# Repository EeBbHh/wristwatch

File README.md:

Disclaimer. This is a work in progress. Open source proof of concept provided. Screenshots and video provided. Documentation is subject to change.

NOTICE! Due to memory limits a second python file was created. sprites.py is required. Place next to code.py in the CIRCUITPY drive. The follwing lines need to be added to boot.py: "import displayio" and below that "displayio.release_displays()"

Clock + Metronome + Tuner wristwatch is the goal of this project. In addition. There are standalone files for each mode.

Dev Enviornment: Mu https://codewith.mu/en/, KiCAD https://www.kicad.org/

Circuitpython for QTpy RP2040: https://circuitpython.org/board/adafruit_qtpy_rp2040/

Circuitpython 10.x libraries: https://circuitpython.org/libraries

NOTE: Place the following in the lib folder: adafruit_bus_device folder, adafruit_display_text folder, adafruit_gc9a01a.mpy and adafruit_ticks.mpy. 

NOTE: Add the following to the requirements folder: adafruit_bus_device folder, adafruit_display_text folder and adafruit_gc9a01a folder.

Microcontroller: QTpy RP2040 https://www.adafruit.com/product/4900

Special thanks to these two projects that got me started on this journey. https://projecthub.arduino.cc/petbump10/arduino-tick-tock-metronome-a49188 and https://github.com/FoamyGuy/Adafruit_CircuitPython_Display_AnalogClock

Prototype 1, 2 and 3 Display: 1.28" Round TFT https://www.adafruit.com/product/6178 

Prototype 1 hardware: EYESPI BFF https://www.adafruit.com/product/5772, IoT Button BFF https://www.adafruit.com/product/5666, Vibration Mini Motor https://www.adafruit.com/product/1201, Piezo Buzzer https://www.adafruit.com/product/1740, LIPO Charger BFF https://www.adafruit.com/product/5397, 400mAh LIPO Battery https://www.adafruit.com/product/3898

Prototype 2 hardware: IoT Button BFF removed. Prototype board added. SMD parts replace THT parts. All SMD parts purchsed from https://www.digikey.com/ Buttons added. Piezo replaced with magnetic transducer. Schematic and board file provided. 

Prototype 3 hardware: EYESPI BFF removed. Prototype board updated. SMD FPC added. SMD vibration motor replaces THT vibration motor. 420mAh LIPO battery https://www.adafruit.com/product/4236 replaces 400mAh LIPO battery. 

Prototype 4 hardware: Prototype board updated. New 1.28 Display https://www.buydisplay.com/1-28-inch-tft-lcd-display-240x240-round-circle-screen-for-smart-watch, SMD FPC updated. QTpy dock added. Futher refinement is underway as I put protoboardV4 through testing.

Prototype 5 hardware: Circuit for display reset added. Circuit for backlight added. QTpy dock adjusted from 17.5mm to 18mm. Prototype board version 5 sits at 25mm. 

Prototype 6 hardware: Lipo BFF circuitry absorbed to further reduce height of the stack. Final iteration for 6 will have the female headers removed and vibration motor moved out of the way for soldering the QTpy closer to the board. Prototype board version 6 sits at 11.30mm. Goal is to get closer to 13 with case.

Prototype 7 hardware: Through hole side actuated buttons replaced Surface mount top actuated buttons. Test pads replaced through hole connectors for battery.

https://github.com/user-attachments/assets/00a04122-98c7-4e2a-a195-a43d13c6c467

Vibration circuit layout. A transistor and resistor are used to make it possible for the QTpy to control the motor with 3 volts. A diode is used as a flyback for when the motor stops running. The transistor connects to the black wire, the resistor and the diode. The black wire goes from the emitter lead of the transistor to ground. The resistor(100ohm) connects the base lead of the transistor to A1. The anode portion of the diode connects to the collector lead of the transistor. The cathode porton of the diode connects to the red wire. The red wire connects to 3.3 volts. The driver motor connects to each side of the diode. Blue to anode and red to cathode. 

Component list: 100Ω resistor, diode(1N4007) and transistor(2N2222)

Soldered vibration circuit.

https://github.com/user-attachments/assets/0c229e03-611d-4f90-9194-24d2ad153cdb

Soldered piezo.

https://github.com/user-attachments/assets/ea14efcf-dfc6-47f1-8c45-b138b7211cc2

LIPO BFF added. Backlight hack added(red wire at the top) to allow for screen dimming as a battery saving feature.

Screen dimming test. At the 10 second mark the screen dims.

https://github.com/user-attachments/assets/76fc044c-b8f3-486a-8c0e-50453308a22c

Prototype 2 board screenshots. Pre and post solder.

Prototype 3 board screenshots. Pre and post solder.

Prototype 4a board screenshots. Pre and post solder.

Prototype 5a board screenshots. Pre and post solder.

Prototype 5b board screenshots. Pre and post solder.

Prototype 6a board screenshots. Pre and post solder.

Prototype 6b board screenshots. Pre and post solder.

Prototype 6c board screenshots. Pre and post solder.

Prototype 6d board screenshots. Pre and post solder.

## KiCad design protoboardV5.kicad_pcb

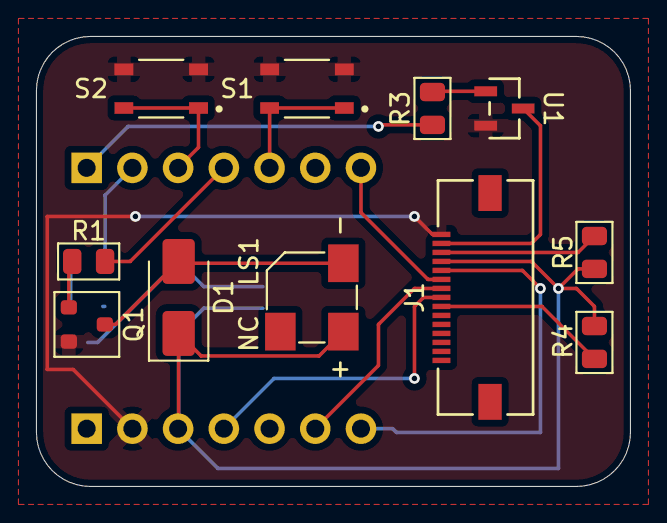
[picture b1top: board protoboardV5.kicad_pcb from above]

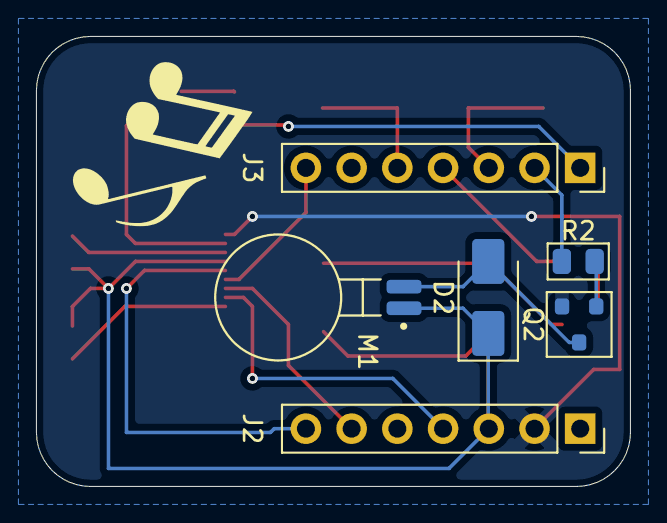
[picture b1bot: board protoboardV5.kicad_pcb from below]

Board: 2 copper layers, 33.0 x 25.0 mm, 17 parts (6 on the bottom side), 19 nets.

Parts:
D1: D1; D_SMA
D2: D2; D_SMA
J1: J1; CON_5051101592_MOL
J2: J2; PinSocket_1x07_P2.54mm_Vertical
J3: J3; PinSocket_1x07_P2.54mm_Vertical
LS1: LS1; CUI_CSS-0575A-SMT
M1: M1; XDCR_C0720B001F
Q1: Q1; SOT-23
Q2: Q2; SOT-23
R1, R2: 100; R_0805_2012Metric
R3, R4: 10k; R_0805_2012Metric
R5: 10; R_0805_2012Metric
S1: S1; SW_SKRPABE010
S2: S2; SW_SKRPABE010
U1: U1; SOT-23_3L_ONS

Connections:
+3.3V: D1.1 (K), D2.1 (K), J1.12, J2.3, LS1.1, M1.1 (V+), R4.1, R5.1
/A0: J3.1, R3.1
/A1: J3.2, R2.1
/A2: J3.3, S2.1, S2.2
/A3: J3.4, R1.1
/MOSI: J1.8, J2.4
/RX: J1.11, J2.7
/SCK: J1.9, J2.6
/SDA: J3.5, S1.1, S1.2
/TX: J1.10, J3.7
GND: J1.15, J2.2, Q1.2 (E), Q2.2 (E), S1.3, S1.4, S2.3, S2.4, U1.2 (S)
unnamed: D1.2 (A), LS1.2, Q1.3 (C)
unnamed: D2.2 (A), M1.2 (V-), Q2.3 (C)
unnamed: J1.7, R4.2
unnamed: J1.13, R5.2
unnamed: Q1.1 (B), R1.2
unnamed: Q2.1 (B), R2.2
unnamed: J1.14, U1.3 (D)
unnamed: R3.2, U1.1 (G)

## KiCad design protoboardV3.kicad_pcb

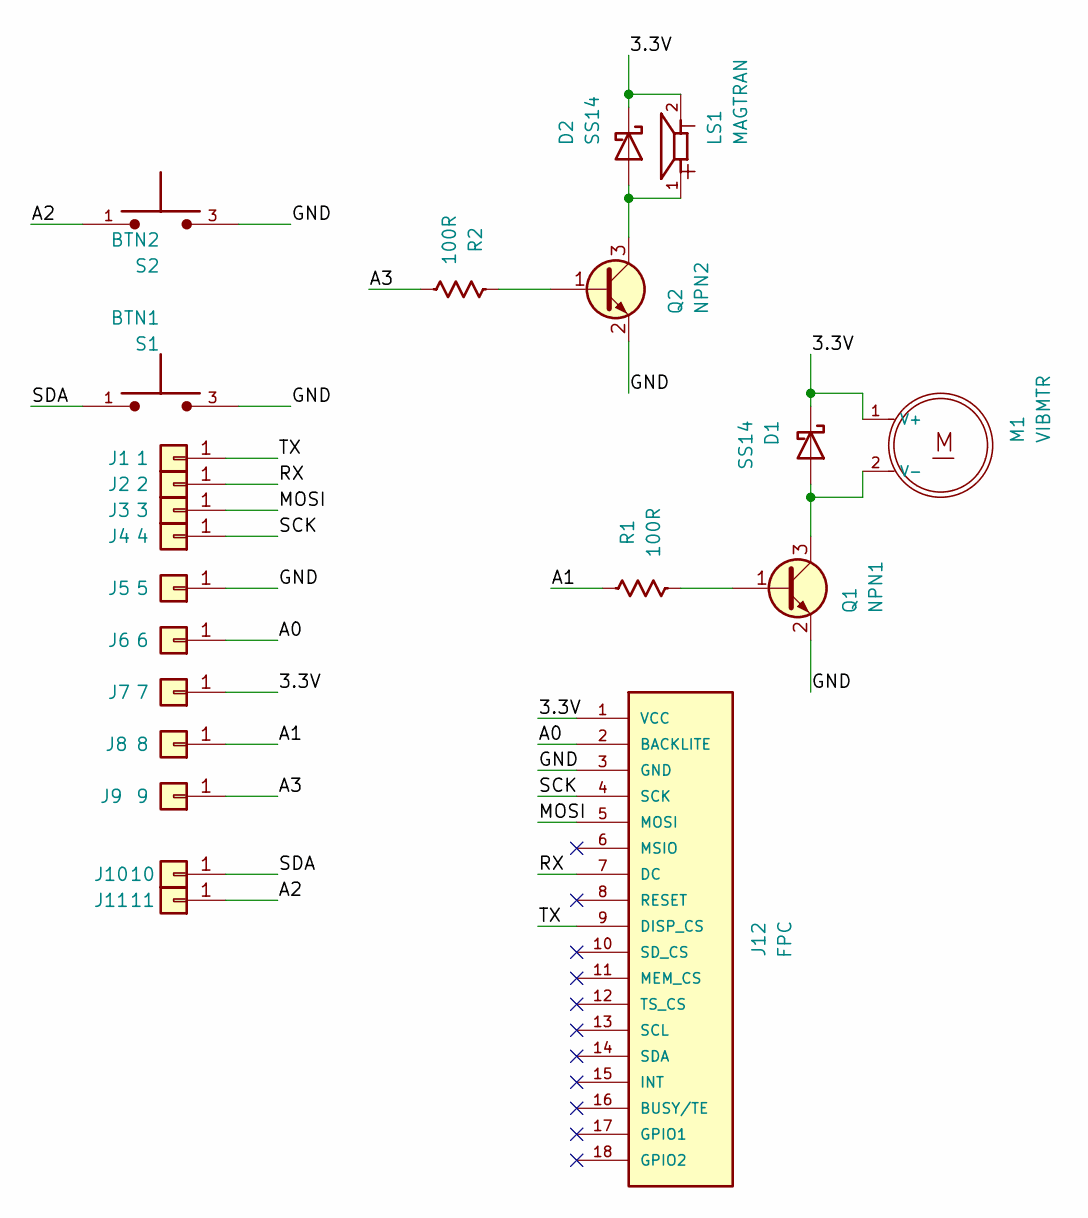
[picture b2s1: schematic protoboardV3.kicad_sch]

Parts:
D1, D2: SS14; D_SMA
J1: 1; 1x01_P2.54mm
J2: 2; 1x01_P2.54mm
J3: 3; 1x01_P2.54mm
J4: 4; 1x01_P2.54mm
J5: 5; 1x01_P2.54mm
J6: 6; 1x01_P2.54mm
J7: 7; 1x01_P2.54mm
J8: 8; 1x01_P2.54mm
J9: 9; 1x01_P2.54mm
J10: 10; 1x01_P2.54mm
J11: 11; 1x01_P2.54mm
J12: FPC; MOLEX_503480-1800; PARTREV J
LS1: MAGTRAN; CUI_CSS-0575A-SMT
M1: VIBMTR; XDCR_C0720B001F
Q1: NPN1; SOT-23
Q2: NPN2; SOT-23
R1, R2: 100R; R_0805_2012Metric
S1: BTN1; SW_SKRPABE010
S2: BTN2; SW_SKRPABE010

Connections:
/3.3V: D1.1 (K), D2.1 (K), J7.1 (Pin_1_1), J12.1 (VCC), LS1.2, M1.1 (V+)
/A0: J6.1 (Pin_1_1), J12.2 (BACKLITE)
/A1: J8.1 (Pin_1_1), R1.1
/A2: J11.1 (Pin_1_1), S2.1, S2.2
/A3: J9.1 (Pin_1_1), R2.1
/GND: J5.1 (Pin_1_1), J12.3 (GND), Q1.2 (E), Q2.2 (E), S1.3, S1.4, S2.3, S2.4
/MOSI: J3.1 (Pin_1_1), J12.5 (MOSI)
/RX: J2.1 (Pin_1_1), J12.7 (DC)
/SCK: J4.1 (Pin_1_1), J12.4 (SCK)
/SDA: J10.1 (Pin_1_1), S1.1, S1.2
/TX: J1.1 (Pin_1_1), J12.9 (DISP_CS)
unnamed: D1.2 (A), M1.2 (V-), Q1.3 (C)
unnamed: D2.2 (A), LS1.1, Q2.3 (C)
unnamed: Q1.1 (B), R1.2
unnamed: Q2.1 (B), R2.2

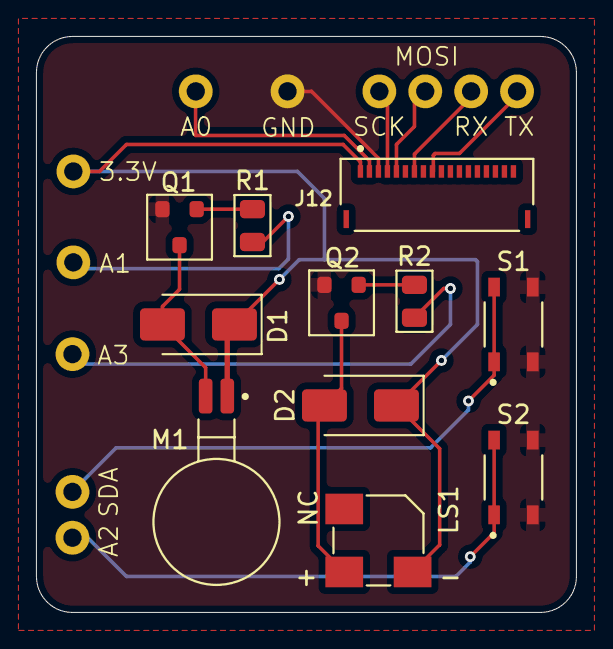
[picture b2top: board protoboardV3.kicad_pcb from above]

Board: 2 copper layers, 30.0 x 32.0 mm, 22 parts (0 on the bottom side), 15 nets.

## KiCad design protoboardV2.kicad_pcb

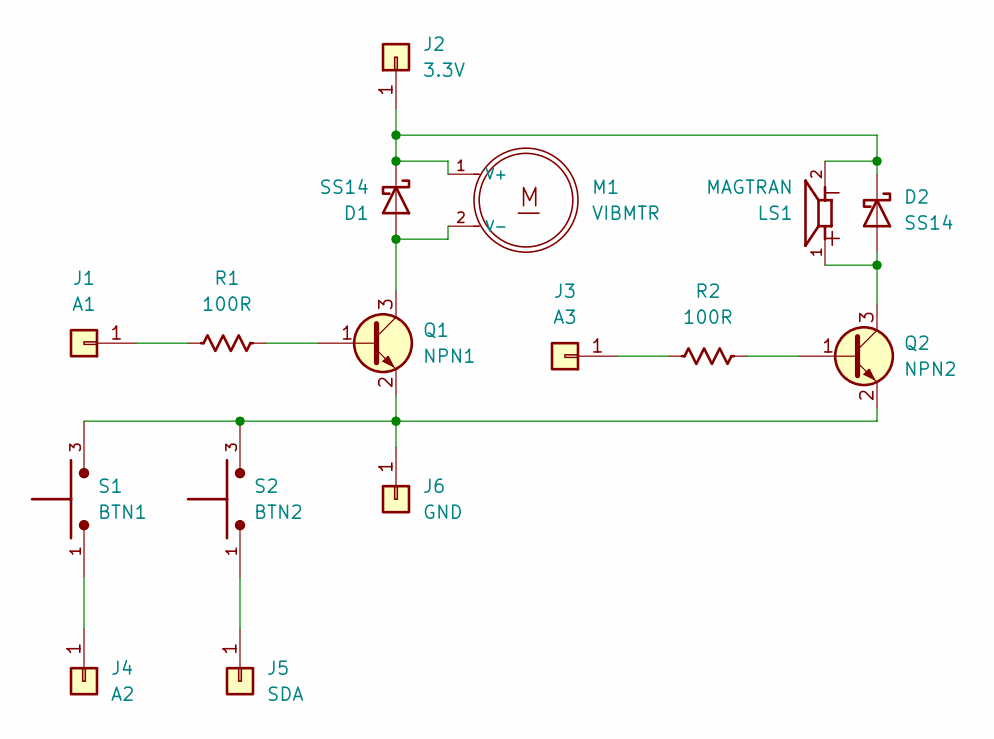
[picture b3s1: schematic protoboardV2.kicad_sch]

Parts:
D1, D2: SS14; D_SMA
J1: A1; Pin_D1.0mm_L10.0mm_LooseFit
J2: 3.3V; Pin_D1.0mm_L10.0mm_LooseFit
J3: A3; Pin_D1.0mm_L10.0mm_LooseFit
J4: A2; Pin_D1.0mm_L10.0mm_LooseFit
J5: SDA; Pin_D1.0mm_L10.0mm_LooseFit
J6: GND; Pin_D1.0mm_L10.0mm_LooseFit
LS1: MAGTRAN; CUI_CSS-0575A-SMT
M1: VIBMTR; XDCR_C0720B001F
Q1: NPN1; SOT-23
Q2: NPN2; SOT-23
R1, R2: 100R; R_0805_2012Metric
S1: BTN1; SW_SKRPABE010
S2: BTN2; SW_SKRPABE010

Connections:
unnamed: D1.2 (A), M1.2 (V-), Q1.3 (C)
unnamed: D1.1 (K), D2.1 (K), J2.1 (Pin_1_1), LS1.2, M1.1 (V+)
unnamed: D2.2 (A), LS1.1, Q2.3 (C)
unnamed: J1.1 (Pin_1_1), R1.1
unnamed: J3.1 (Pin_1_1), R2.1
unnamed: J4.1 (Pin_1_1), S1.1, S1.2
unnamed: J5.1 (Pin_1_1), S2.1, S2.2
unnamed: J6.1 (Pin_1_1), Q1.2 (E), Q2.2 (E), S1.3, S1.4, S2.3, S2.4
unnamed: Q1.1 (B), R1.2
unnamed: Q2.1 (B), R2.2

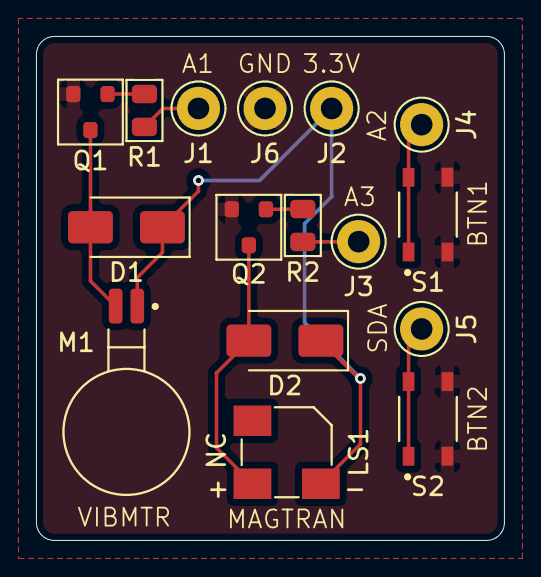
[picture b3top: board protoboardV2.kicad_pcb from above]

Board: 2 copper layers, 26.0 x 28.0 mm, 16 parts (0 on the bottom side), 10 nets.

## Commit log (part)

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2026-03-21 Add files via upload
    first upload of work in progress
2026-03-21 Delete clock metronome tuner.txt
    Replacing with python file.
2026-03-21 Update README.md
    adding screenshots
2026-03-22 Create LICENSE
2026-03-22 Update LICENSE
2026-03-26 Delete clock metronome tuner.py
    replacing with code.py
